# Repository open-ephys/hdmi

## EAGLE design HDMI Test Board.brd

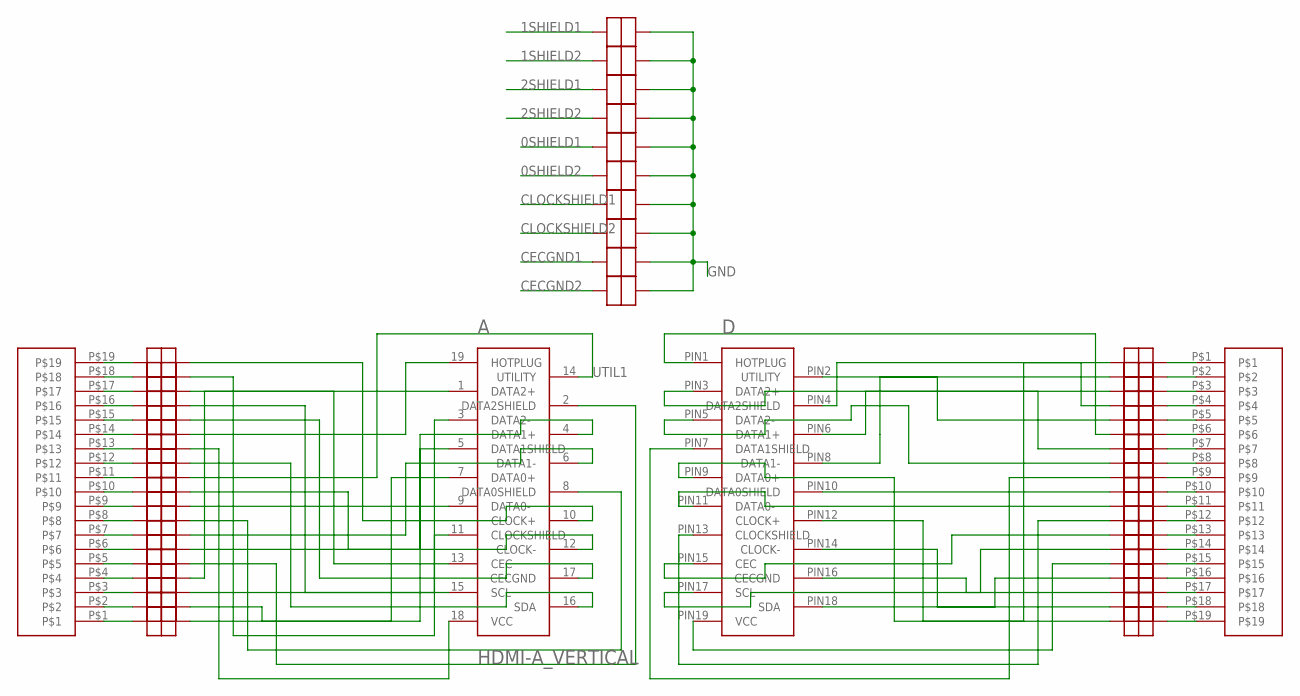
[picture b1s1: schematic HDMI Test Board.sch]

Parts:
A: HDMI-A_VERTICAL; KDMIX-SL
D: HDMI-D; MICRO_HDMI
U$2, U$5, U$6, U$7, U$8, U$9, U$10, U$11, U$12, U$13, U$14, U$15, U$16, U$17, U$18, U$19, U$20, U$21, U$22, U$23, U$24, U$25, U$26, U$27, U$28, U$29, U$30, U$31, U$32, U$33, U$34, U$35, U$36, U$37, U$38, U$39, U$40, U$41, U$42, U$43, U$44, U$45, U$46, U$47, U$48, U$49, U$50, U$51: 1X2-HEADER
U$3, U$4: 1X19-HEADER

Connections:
0+1: A.7 (DATA0+), U$11.P$2
0+2: D.PIN9 (DATA0+), U$30.P$1
0-1: A.9 (DATA0-), U$12.P$2
0-2: D.PIN11 (DATA0-), U$31.P$1
0SHIELD1: A.8 (DATA0SHIELD), U$21.P$2, U$47.P$1
0SHIELD2: D.PIN10 (DATA0SHIELD), U$40.P$1, U$46.P$1
1+1: A.4 (DATA1+), U$9.P$2
1+2: D.PIN6 (DATA1+), U$28.P$1
1-1: A.6 (DATA1-), U$10.P$2
1-2: D.PIN8 (DATA1-), U$29.P$1
1SHIELD1: A.5 (DATA1SHIELD), U$20.P$2, U$51.P$1
1SHIELD2: D.PIN7 (DATA1SHIELD), U$39.P$1, U$50.P$1
2+1: A.1 (DATA2+), U$7.P$2
2+2: D.PIN3 (DATA2+), U$26.P$1
2-1: A.3 (DATA2-), U$8.P$2
2-2: D.PIN5 (DATA2-), U$27.P$1
2SHIELD1: A.2 (DATA2SHIELD), U$19.P$2, U$49.P$1
2SHIELD2: D.PIN4 (DATA2SHIELD), U$38.P$1, U$48.P$1
CEC1: A.13 (CEC), U$15.P$2
CEC2: D.PIN15 (CEC), U$34.P$1
CECGND1: A.17 (CECGND), U$2.P$1, U$16.P$2
CECGND2: D.PIN16 (CECGND), U$35.P$1, U$43.P$1
CLOCK+1: A.10 (CLOCK+), U$13.P$2
CLOCK+2: D.PIN12 (CLOCK+), U$32.P$1
CLOCK-1: A.12 (CLOCK-), U$14.P$2
CLOCK-2: D.PIN14 (CLOCK-), U$33.P$1
CLOCKSHIELD1: A.11 (CLOCKSHIELD), U$22.P$2, U$45.P$1
CLOCKSHIELD2: D.PIN13 (CLOCKSHIELD), U$41.P$1, U$44.P$1
GND: U$2.P$2, U$43.P$2, U$44.P$2, U$45.P$2, U$46.P$2, U$47.P$2, U$48.P$2, U$49.P$2, U$50.P$2, U$51.P$2
HOTPLUG1: A.19 (HOTPLUG), U$5.P$2
HOTPLUG2: D.PIN1 (HOTPLUG), U$24.P$1
unnamed: U$4.P$14, U$5.P$1
unnamed: U$4.P$11, U$6.P$1
unnamed: U$4.P$4, U$7.P$1
unnamed: U$4.P$3, U$8.P$1
unnamed: U$4.P$6, U$9.P$1
unnamed: U$4.P$7, U$10.P$1
unnamed: U$4.P$1, U$11.P$1
unnamed: U$4.P$19, U$12.P$1
unnamed: U$4.P$9, U$13.P$1
unnamed: U$4.P$10, U$14.P$1
unnamed: U$4.P$17, U$15.P$1
unnamed: U$4.P$15, U$16.P$1
unnamed: U$4.P$16, U$17.P$1
unnamed: U$4.P$12, U$18.P$1
unnamed: U$4.P$5, U$19.P$1
unnamed: U$4.P$2, U$20.P$1
unnamed: U$4.P$8, U$21.P$1
unnamed: U$4.P$18, U$22.P$1
unnamed: U$4.P$13, U$23.P$1
unnamed: U$3.P$6, U$24.P$2
unnamed: U$3.P$5, U$25.P$2
unnamed: U$3.P$7, U$26.P$2
unnamed: U$3.P$8, U$27.P$2
unnamed: U$3.P$3, U$28.P$2
unnamed: U$3.P$2, U$29.P$2
unnamed: U$3.P$10, U$30.P$2
unnamed: U$3.P$11, U$31.P$2
unnamed: U$3.P$19, U$32.P$2
unnamed: U$3.P$18, U$33.P$2
unnamed: U$3.P$13, U$34.P$2
unnamed: U$3.P$17, U$35.P$2
unnamed: U$3.P$14, U$36.P$2
unnamed: U$3.P$16, U$37.P$2
unnamed: U$3.P$4, U$38.P$2
unnamed: U$3.P$9, U$39.P$2
unnamed: U$3.P$1, U$40.P$2
unnamed: U$3.P$12, U$41.P$2
unnamed: U$3.P$15, U$42.P$2
SCL1: A.15 (SCL), U$17.P$2
SCL2: D.PIN17 (SCL), U$36.P$1
SDA1: A.16 (SDA), U$18.P$2
SDA2: D.PIN18 (SDA), U$37.P$1
UTIL1: A.14 (UTILITY), U$6.P$2
UTILITY2: D.PIN2 (UTILITY), U$25.P$1
VCC1: A.18 (VCC), U$23.P$2
VCC2: D.PIN19 (VCC), U$42.P$1

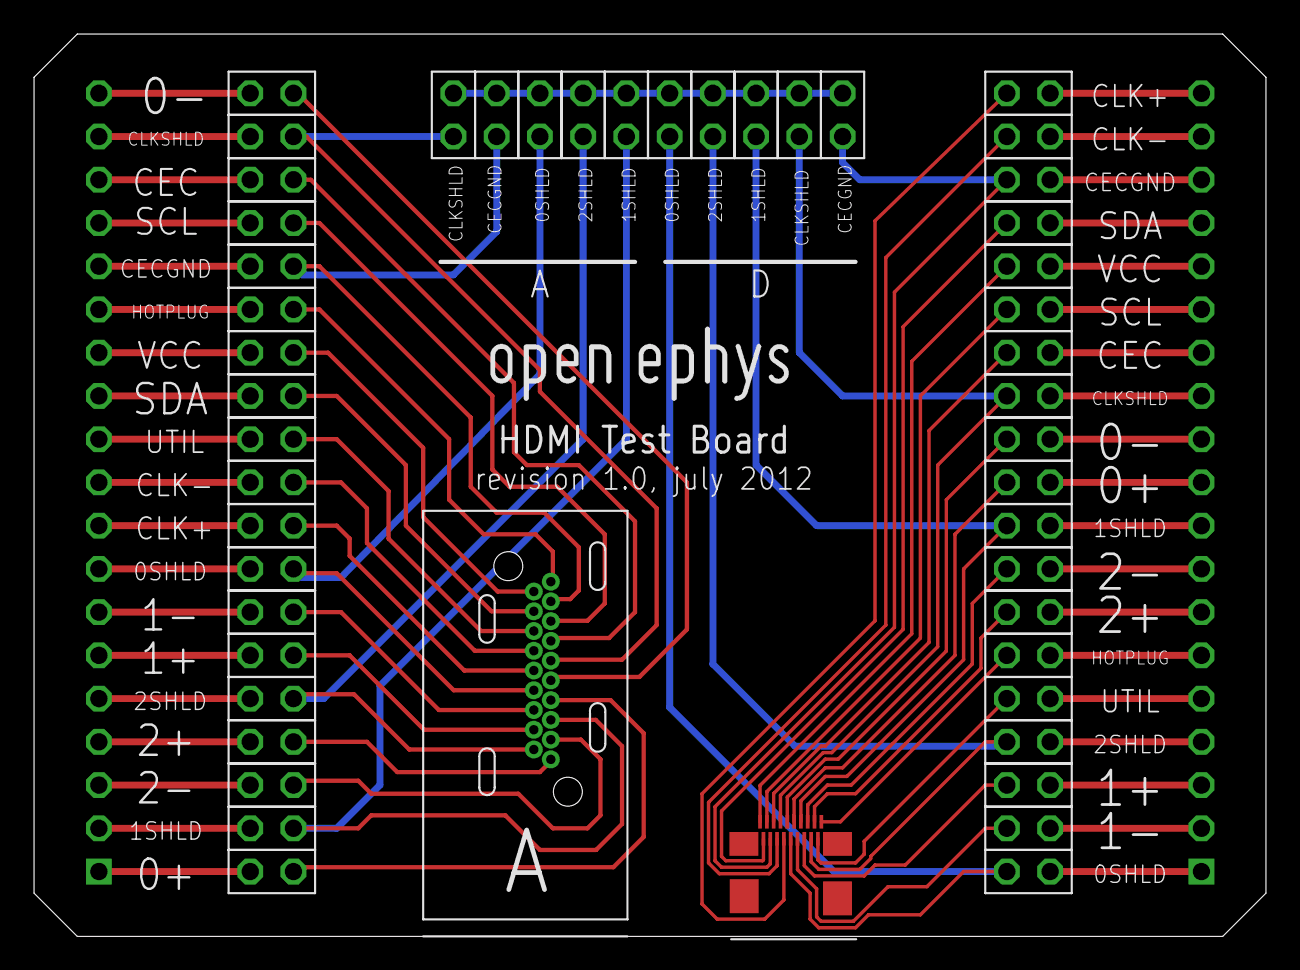
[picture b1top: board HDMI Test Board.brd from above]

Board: 2 copper layers, 72.4 x 53.0 mm, 53 parts (0 on the bottom side), 77 nets.

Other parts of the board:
U$1: OPEN_EPHYS_LOGO
